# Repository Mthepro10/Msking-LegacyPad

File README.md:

# Msking-LegacyPad
I wanted to create my first keyboard and I hope you like it! I struggled a bit, more at the case (since it is my first time using fusion 360) but now i am ready.

# SCHEMATIC and PCB

# CASE

# Firmware
The firmware was made in KMK.

# BOM
+ 1x Seeed XIAO RP2040 (through-hole)
+ 10x Through-hole 1N4148 Diodes
+ 9x MX-Style switches + 9x Blank DSA keycaps
+ 1x EC11 Rotary encoders
+ 1x 0.91 inch OLED SSD1306 (5V VCC, 3.3V logic, I2C)
+ 1x SK6812 MINI-E LEDs
+ 4x M3x16 Bolt + 4x M3 Heatset

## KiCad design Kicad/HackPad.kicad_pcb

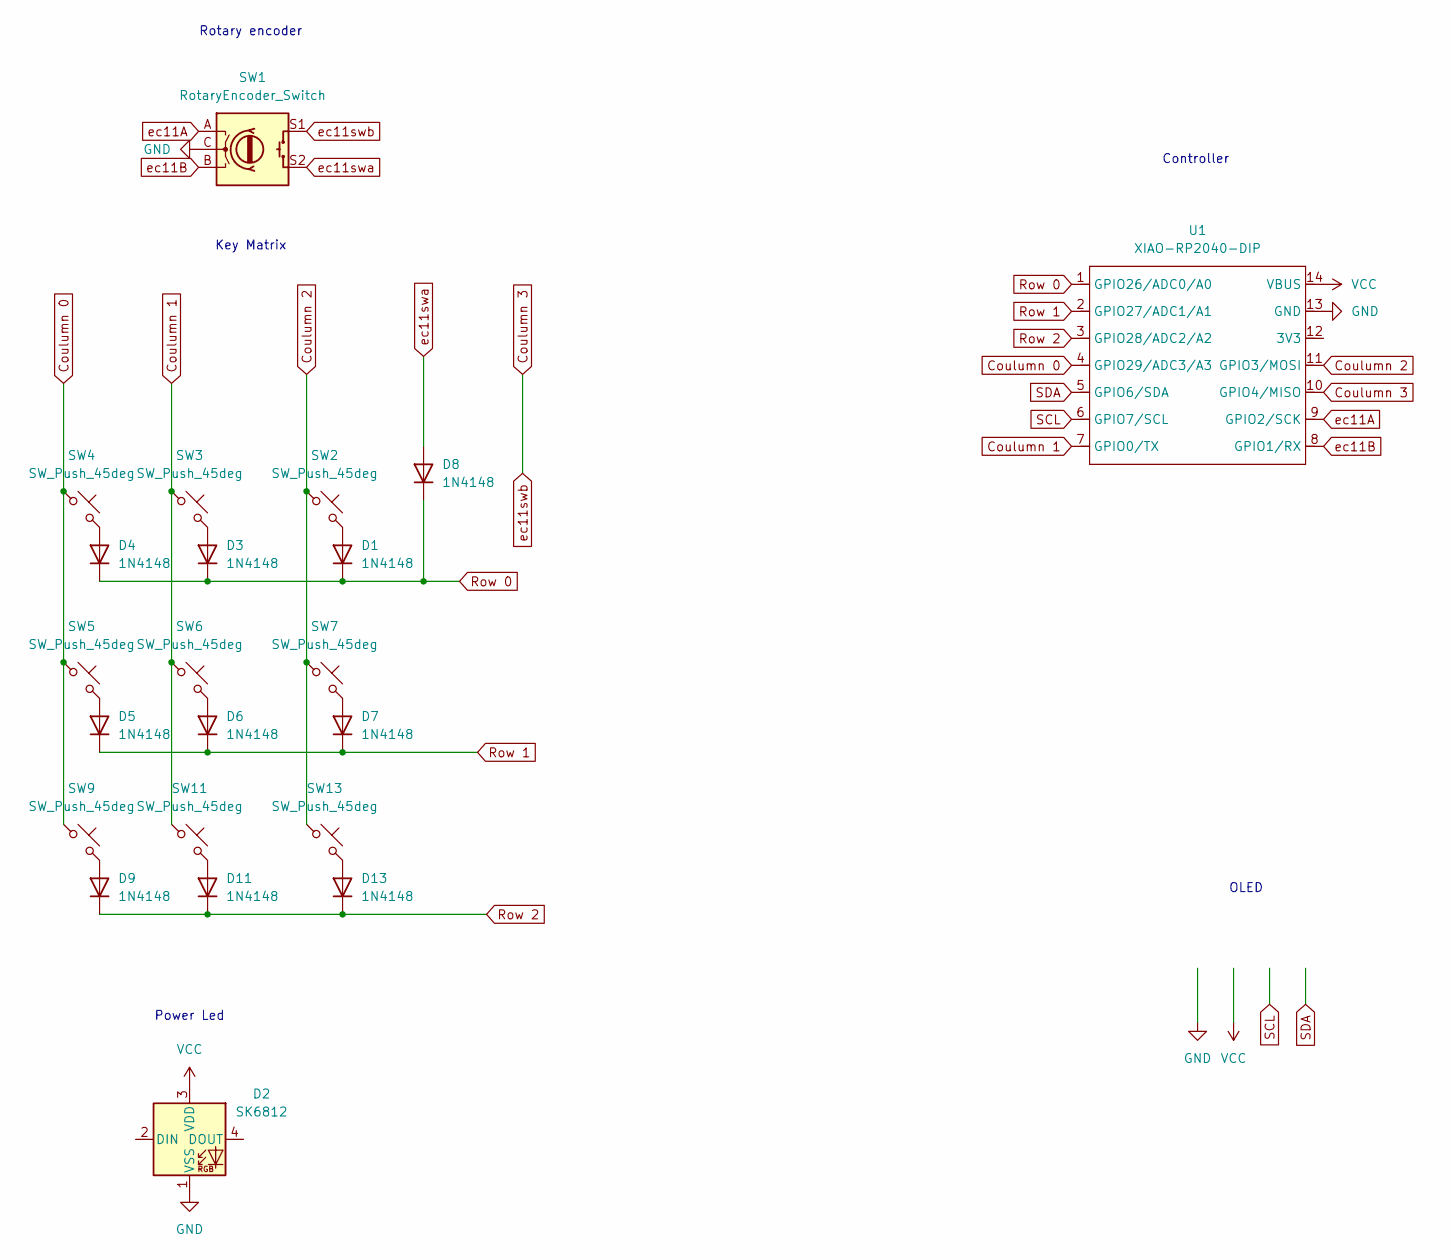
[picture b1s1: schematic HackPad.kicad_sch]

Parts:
D1, D3, D4, D5, D6, D7, D8, D9, D11, D13: 1N4148; D_DO-35_SOD27_P7.62mm_Horizontal
D2: SK6812; LED_SK6812_PLCC4_5.0x5.0mm_P3.2mm
SW1: RotaryEncoder_Switch; RotaryEncoder_Alps_EC11E-Switch_Vertical_H20mm
SW2, SW3, SW4, SW5, SW6, SW7, SW9, SW11, SW13: SW_Push_45deg; SW_Cherry_MX_1.00u_PCB
U1: XIAO-RP2040-DIP

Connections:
Coulumn 0: SW4.1, SW5.1, SW9.1, U1.4 (GPIO29/ADC3/A3)
Coulumn 1: SW3.1, SW6.1, SW11.1, U1.7 (GPIO0/TX)
Coulumn 2: SW2.1, SW7.1, SW13.1, U1.11 (GPIO3/MOSI)
Coulumn 3: SW1.S1, U1.10 (GPIO4/MISO)
GND: D2.1 (VSS), SW1.C, U1.13 (GND); also elsewhere on the board
unnamed: D1.2 (A), SW2.2
unnamed: D3.2 (A), SW3.2
unnamed: D4.2 (A), SW4.2
unnamed: D5.2 (A), SW5.2
unnamed: D6.2 (A), SW6.2
unnamed: D7.2 (A), SW7.2
unnamed: D9.2 (A), SW9.2
unnamed: D11.2 (A), SW11.2
unnamed: D13.2 (A), SW13.2
Row 0: D1.1 (K), D3.1 (K), D4.1 (K), D8.1 (K), U1.1 (GPIO26/ADC0/A0)
Row 1: D5.1 (K), D6.1 (K), D7.1 (K), U1.2 (GPIO27/ADC1/A1)
Row 2: D9.1 (K), D11.1 (K), D13.1 (K), U1.3 (GPIO28/ADC2/A2)
SCL: U1.6 (GPIO7/SCL); also elsewhere on the board
SDA: U1.5 (GPIO6/SDA); also elsewhere on the board
VCC: D2.3 (VDD), U1.14 (VBUS); also elsewhere on the board
ec11A: SW1.A, U1.9 (GPIO2/SCK)
ec11B: SW1.B, U1.8 (GPIO1/RX)
ec11swa: D8.2 (A), SW1.S2

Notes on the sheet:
Rotary encoder
OLED
Key Matrix
Power Led
Controller

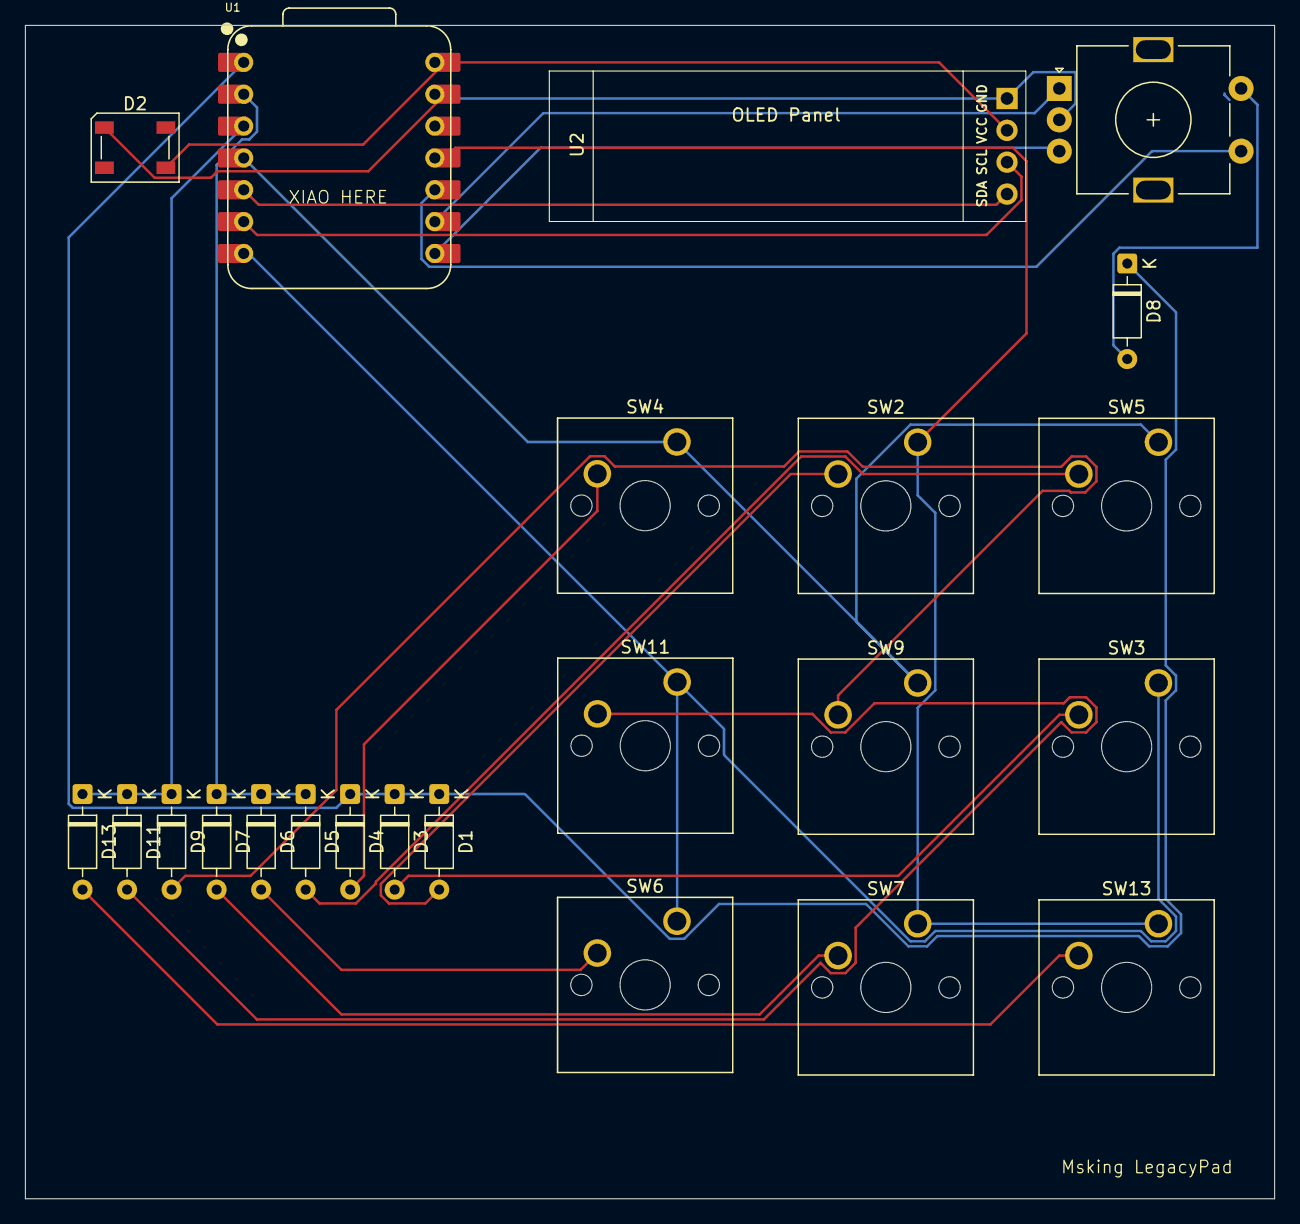
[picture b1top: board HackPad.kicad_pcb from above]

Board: 2 copper layers, 99.6 x 93.6 mm, 23 parts (0 on the bottom side), 23 nets.

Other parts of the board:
U2: SSD1306; SSD1306-0.91-OLED-4pin-128x32

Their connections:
GND: U2.1 (C2P); also elsewhere on the board
SCL: U2.3 (C1P); also elsewhere on the board
SDA: U2.4 (C1N); also elsewhere on the board
VCC: U2.2 (C2N); also elsewhere on the board

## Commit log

2025-12-26 Mesaj despre modificări
